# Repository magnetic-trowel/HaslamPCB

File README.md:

# HaslamPCB

Turns a product description into a manufacturable KiCad board. An LLM (or a person) writes the circuit as
Python; the tools produce the schematic, place and route the board, score its physics, and write JLCPCB
fabrication files. No step calls an LLM: every decision is a command with a traceable result.

- **[Part 1: Design a PCB](#part-1-design-a-pcb)**: use the tools on your own board.
- **[Part 2: Improve haslam](#part-2-improve-haslam)**: change the placer, router or physics and prove the change helps.

| Part | Path | Does |
|---|---|---|
| haslamsynth | `tools/research/llm-design/synth/` | circuit code → checked KiCad schematic, rules, BOM, operating intent |
| haslam | `haslam/` | placement, routing, physics evaluation |
| haslamq | `tools/haslamq/` | job queue for a shared host |
| haslamres, haslambench | `tools/haslamres/`, `bench/` | benchmark corpus, results store, experiments |

## Setup (Ubuntu, no sudo)

```bash
bench/scripts/setup.sh --all                 # KiCad 10 (apt with sudo, else Apptainer), the Freerouting fork of
                                             # bench/freerouting.ref, bench/haslam/synth venvs, ~/.cache/haslambench/env.sh
source bench/.venv/bin/activate && haslambench doctor --pipeline   # every piece below, checked
```

`env.sh` exports everything the pipeline reads: `HASLAM_HOME`, `HASLAM_KICAD_WRAP` (empty with a native KiCad; run KiCad
as `$HASLAM_KICAD_WRAP kicad-cli …` or `$HASLAM_KICAD_WRAP python3`), `KICAD10_SYMBOL_DIR`/`KICAD10_FOOTPRINT_DIR`, and with a
container KiCad `APPTAINER_BIND` (the checkout; set it yourself for a work dir elsewhere). Every shell and job:
`source ~/.cache/haslambench/env.sh`, KiCad under `ulimit -v 40000000`. The synth venv has `haslam/src` on its path; the
haslam venv has haslam installed, so no `PYTHONPATH` is needed.

On a shared host, run anything over about ten minutes or two cores through haslamq (`tools/haslamq/README.md`):
`haslamq submit --cpus N --mem XG --timeout T --owner <name> -- CMD`, then one background `haslamq wait`. Jobs run a
frozen snapshot of the checkout. Retry and cancel your own jobs only, by id or `--owner`. On a single-user machine (your
own computer, a cloud container without haslamq), run the same commands directly, long ones in the background.

---

# Part 1: Design a PCB

A design lives in `tools/research/llm-design/designs/<slug>/` (example: `solar-small`). **This table is the canonical
stage list**; [brief-to-board](docs/topics/workflow/brief-to-board.md) holds the worked example and failure modes, and
[synth/README.md](tools/research/llm-design/synth/README.md) the `design.py` API. Stages 3-11 run through
`synth/scripts/pipeline.py`, from the repo root in the haslam venv with `env.sh` sourced:

```bash
P="haslam/.venv/bin/python tools/research/llm-design/synth/scripts/pipeline.py tools/research/llm-design/designs/<slug>"
$P status          # every gate and the next stage
$P build           # then board, preflight, size, layout (once per seed), physics, warnings, review, fab
```

`pipeline.py` records each gate in `haslam-work/<slug>/pipeline/status.json`, refuses a stage while an earlier gate is
unmet or older than `design.py`/`parts.py`/`board.json`, and writes fabrication files only for a board that passed
every gate. Script paths below are relative to `tools/research/llm-design/synth/scripts/`.

| # | Stage | `pipeline.py` stage: what it runs | Gate |
|---|---|---|---|
| 1 | Requirements and parts | (you) read datasheets (tables and figures, not summaries); check stock and basic/extended status with the JLC parts API | every number has a page citation |
| 2 | Circuit as code | (you) `designs/<slug>/parts.py` (part cards), `design.py` (blocks, nets, placement relations, intent; `haslamsynth api` lists every call), `board.json` (outline, holes, fixed parts, pours, keepouts), custom footprints | — |
| 3 | Schematic and checks | `build`: `haslamsynth jlc` (LCSC numbers of generic passives, `jlc.json`), then `haslamsynth build -v` → `designs/<slug>/out/`: `.kicad_sch`, `.kicad_pro`, `.kicad_dru`, `bom.csv`, `report.md`, `<slug>.haslam_intent.json` | exit 0: 0 unwaived errors (incl. `rules.pin_escape`, `rules.pad_gap`), ERC clean, netlist round trip identical; read every warning in `report.md` |
| 4 | Unplaced board | `board`: `sch_to_board.py out board.json` at the `size` stage's best outline, else `board.json`'s | board written |
| 5 | Pre-flight | `preflight`: `preflight.py <board> --probe` (KiCad and Freerouting reachable, rules parse, schematic parity, fixed parts legal, fab profile, intent, a 3-minute place-and-route probe) | 0 FAIL; read each WARN and `blocked:` line. This is the unplaced board's gate: a plain DRC lists every unplaced part |
| 6 | Board size | `size`: `size_search.py` (start at 25 % courtyard density, shrink while DRC and `width_check.py` pass; resumable) | a passing outline |
| 7 | Layout | `layout --seed N`: `layout.sh <board> <run> <seed>` (place, route, DRC, `width_check.py`; minutes to hours) | ≥ 3 seeds routed; the best has 0 DRC errors, 0 unconnected and passes `width_check` |
| 8 | Physics | `physics`: `haslam.excite.evaluate` + `haslam.intent status` on the best seed | evaluation complete; no `hard` term violated |
| 9 | DRC warnings | `warnings`: the best seed's DRC warnings by type | each type listed in `designs/<slug>/drc_warnings.json` with a reason |
| 10 | Review | `review`: an independent review | `designs/<slug>/REVIEW.md` newer than `design.py` and `parts.py` |
| 11 | Fabrication | `fab`: `fab_outputs.py` (zone refill, DRC, Gerbers, drill, CPL, BOM) | fab-report gate passes; no blocking question open in `report.md`; `fab-report.json` lists extended parts (each a JLC setup fee) |

Where to run the long stages (`size`, `layout`, `physics`): on a single-user machine run `$P layout --seed N`
directly (in the background); on a shared host submit each through haslamq (`haslamq submit … -- $P layout --seed N`)
and wait with one background `haslamq wait`. Comparing seeds or design variants side by side (DRC by type, open
connections, every physics term): `compare_ab.py <rundir> --md table.md`.
`designs/solar-small/run_ab.sh` is solar-small's own A/B of layout recipes, not a stage.

**How each stage works** (by name; stages 1-2 are yours, the rest are `pipeline.py` stages)

- **Requirements and parts.** The designer (often an LLM) turns the product brief into numbers (voltages, currents,
  switching frequencies, limits) and picks parts that JLCPCB can assemble, preferring basic parts, which have no
  per-order setup fee.
- **Circuit as code.** The circuit is Python: part cards carry each part's pins, footprint, ratings and datasheet facts;
  `design.py` connects them into blocks and nets and states what the board must achieve; `board.json` gives the
  outline and anything mechanical that cannot move (connectors, holes, the module socket).
- **Schematic and checks.** Generic resistors and capacitors are matched to in-stock JLC parts by value, package,
  voltage and dielectric. haslamsynth checks the circuit (ratings against operating stress, ERC, netlist round trip)
  and writes the KiCad project. It derives clearance rules per net pair from each net's voltage (IPC-2221B) and track
  minimums from the finest pad pitch, and proves every pin can still escape under them. It also writes the **operating
  intent** (`<slug>.haslam_intent.json`, beside the board like `.kicad_pro`): the facts haslam cannot read from copper (rail
  voltages; each converter's input, output, current and switching frequency; cables) and the requirements, as terms
  with tiers (`hard` limits, `limit` budgets, `cost`). `python -m haslam.cli brief <board>` shows how haslam reads them.
- **Unplaced board.** The netlist becomes a `.kicad_pcb` with every footprint, the fixed parts in place, pours,
  keepouts and the fab's stackup (JLC 2-layer 1.6 mm FR-4 unless `board.json` `stackup` says otherwise).
- **Pre-flight.** A few minutes of checks catch what would waste a long run: KiCad and Freerouting reachable, rules
  accepted by KiCad, schematic parity, fixed parts legal, intent complete, and a short place-and-route probe that
  lists any connection the rules block.
- **Board size.** The outline is edge-anchored (`board_spec.py`), so the search can shrink it and re-place the fixed
  parts without hand edits.
- **Layout.** haslam places the parts (an annealer with legality checks, priced by wire length, physics terms
  and routability), routes them (Freerouting plus haslam's repair and last-mile router, which respect pad-entry,
  thermal-spoke and clearance rules), and restarts with new seeds while connections stay open, on a budget of counted
  work rather than wall time. KiCad's DRC and the width check (IPC-2221 width against each net's current) judge the
  routed board.
- **Physics.** haslam's evaluator solves the copper (layered, with 3D inductance and the stackup's capacitance) with
  every converter as a noise source and reports pickup, overshoot, emissions, losses and temperatures against the
  intent's terms. An incomplete evaluation (`why_incomplete`) prices nothing it could not compute.
- **DRC warnings and review.** Every DRC warning type gets a written reason, and an independent reviewer reads the
  design, so a board that passes the checks is still read by someone who did not write it.
- **Fabrication.** Zones are refilled, DRC must pass, and the Gerbers, drill files, pick-and-place file and BOM with
  LCSC numbers are written in JLCPCB's formats.

Judge every result by KiCad's DRC and the evaluator on the re-opened board, never by a tool's own log.

---

# Part 2: Improve haslam

haslam is improved by experiment: a change is adopted when it measurably helps on benchmark boards, paired against a
control, and never by changing how results are scored.

**Extra setup.** The corpus and harness: `source bench/.venv/bin/activate && haslambench doctor`; boards in the corpus
directory, results in `$HASLAM_RESULTS` (default `~/haslam-baselines`, `tools/haslamres/README.md`). Unit tests:
`haslam/.venv/bin/pytest haslam/tests`, `pytest bench/tests`.

**Procedure** (`docs/topics/verification/experiment-tiers.md`, `bench/suites/README.md`):

1. Branch off the weekly baseline tag (`baseline/<year>-w<week>`), make one change, add tests, push.
2. Write `$HASLAM_RESULTS/experiments/<name>/PLAN.md`: the question, the change, the suite, the primary endpoint, guards.
3. Choose the boards. A change that acts on every board runs on the sprint suites; a change to one mechanism (BGA escape,
   pours, converters, …) runs on `bench/suites/mech/<mechanism>.txt`. Limits: at most 40 CPU-h per campaign, no board
   over 0.5 CPU-h per run; larger tiers (ladder, canary) only after a sprint result.
4. Run: `python3 tools/haslamres/haslamres.py sprint <name> --base bridge|staged --commit <sha>` runs your arm against the
   stored control's runs. Smoke one or two boards first and read their runs.
5. Verdict, paired per board and seed: better, worse or undecided, with an interval, in `VERDICT.md`. Mixed results
   get a per-board look before anything is concluded.

**Rules that keep results comparable**

- Scoring code (`bench/src/haslambench/score.py`, the evaluators) defines the benchmark. A fix to it is its own commit that
  says why, and stored results are re-scored, not re-run.
- Every arm runs at the same tag, with the same Freerouting build, on counted-work budgets, side by side.
- A method's only score is `kicad-cli` on its re-opened output board.

Background: [`docs/INDEX.md`](docs/INDEX.md) (digests, then topic docs; `research_notes/` is raw evidence).

## License

Code is [GPL-3.0-or-later](LICENSE); docs and research notes CC-BY-4.0, rule packs CC0-1.0, datasets CDLA-Permissive-2.0,
model weights Apache-2.0 ([`LICENSING.md`](LICENSING.md); [`CONTRIBUTING.md`](CONTRIBUTING.md), DCO sign-off).

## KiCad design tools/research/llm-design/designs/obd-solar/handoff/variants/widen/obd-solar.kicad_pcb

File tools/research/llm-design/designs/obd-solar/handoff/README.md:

<!-- SPDX-FileCopyrightText: 2026 HaslamPCB contributors -->
<!-- SPDX-License-Identifier: CC-BY-4.0 -->
# obd-solar handoff package: boards, evaluations and how to reproduce

Scope: every file needed to study obd-solar's power-net track widths without rebuilding it. The findings are in
[docs/research/routing/power-net-track-width.md](../../../../../../docs/research/routing/power-net-track-width.md); the
run's friction log is [../FRICTION.md](../FRICTION.md); the circuit is [../design.py](../design.py) and
[../parts.py](../parts.py) (explained in [../DESIGN.md](../DESIGN.md), reviewed in [../REVIEW.md](../REVIEW.md)).
Keys: obd-solar handoff, board package, routed board, width_check, reproduction

These boards are this project's own design (GPL-3.0-or-later, like the rest of `designs/`), not corpus boards, so they
may be committed. Generated on branch `obd-solar-e2e` with KiCad 10.0.8 and the Freerouting fork pinned at 06d2686.

## Contents

| Path | What | Made by |
|---|---|---|
| `unplaced/obd-solar.kicad_pcb` | 96 x 66 mm, 2-layer JLC stackup, 94 footprints, fixed connectors, GND pours, nothing placed or routed | `haslamsynth build` + `sch_to_board.py` (outline 96 x 66) |
| `unplaced/obd-solar.kicad_pro`, `.kicad_dru` | net classes sized from each net's current (10 C rise), JLC fab profile (board setup + FAB rules), functional spacing rules | haslamsynth |
| `unplaced/obd-solar.haslam_intent.json` | operating facts (rails, 3 commutation cells, J301 load 1 A typ / 2 A max), terms (FB/MPPT pickup, overshoot, heat.track 20 K, drop.rail VBUS 150 mV, Tj), 35 placement relations (hot loops as requested near) | haslamsynth |
| `unplaced/netlist.json` | every pin's net, each net's `i_max`, `board.trace_rise_c` | haslamsynth |
| `unplaced/bom.csv`, `fp-lib-table`, `sym-lib-table` | BOM with LCSC numbers; library tables (custom footprints in `../footprints/custom.pretty`) | haslamsynth |
| `routed-s1/obd-solar.kicad_pcb` | seed 1 of `layout.sh` (restart.py recipe, HASLAM_TIME 1200), **before** any power-copper post-pass; this is the board measured in the research doc | `layout.sh` |
| `routed-s1/eval/drc.json` | KiCad DRC with schematic parity: 4 `starved_thermal`, 0 unconnected, parity 0 | kicad-cli |
| `routed-s1/eval/width.json`, `width.txt` | branch-current width gate: 7 nets too narrow (VBAT 69.7 mm, VBUS 20.9, CHG_OUT 41.7, BB_SW2 25.8, OBD_RAW 8.6, BB_SW1 6.8, ...) | `width_check.py` |
| `routed-s1/eval/excite.json`, `status.json` | physics evaluation (0.125 mm cell windows): hottest track 199.6 K, VBUS drop 266 mV, U301 Tj 185 C, FB pickup 259 mV, copper loss 1.76 W | `haslam.excite.evaluate`, `haslam.intent status` |
| `variants/widen/` | `routed-s1` after `power_copper` (widen mode): VBAT 68.2 / VBUS 15.5 / CHG_OUT 11.2 mm too narrow, DRC 4 | `haslam.route.power_copper` |
| `variants/zones-into-pads/` | after `power_copper --mode vector --vector-out zones --no-neck` (67 zones pour into SMD pads): 65.2 / 11.8 / 8.3 mm, DRC 3 | same |

`width_check.py` takes every net's DC current paths from the evaluator's plan under the intent file beside the board (the
hand-written `width_injections.json` it once needed for the OBD feed, VBAT, PV_IN, CHG_OUT and the switch nodes was removed
once the plan covered them: FRICTION.md #73).

## Reproduce

From the repo root, in the haslam venv with `~/.cache/haslambench/env.sh` sourced and `PYTHONPATH=haslam/src`:

```bash
H=tools/research/llm-design/designs/obd-solar/handoff
python tools/research/llm-design/synth/scripts/width_check.py $H/routed-s1/obd-solar.kicad_pcb $H/unplaced/netlist.json
```

```bash
python -m haslam.route.power_copper $H/routed-s1/obd-solar.kicad_pcb /tmp/pc/obd-solar.kicad_pcb --mode vector --vector-out zones --no-neck
```

Route the unplaced board again (copy `unplaced/` to a work folder first; a renamed board runs on KiCad's default rules):

```bash
HASLAM_TIME=1200 HASLAM_EVAL=0 bash tools/research/llm-design/synth/scripts/layout.sh <work>/obd-solar.kicad_pcb <outdir> 1
```

Rebuild everything from source instead: `python tools/research/llm-design/synth/scripts/pipeline.py tools/research/llm-design/designs/obd-solar build`,
then `board`, `preflight`, `layout` (see the script's docstring for the gates).

## Notes

1. `routed-s1` was placed and routed before the hot-loop `requested` relations and the J301 load fact were added to the
   intent; its copy of the intent file is the current one (used for the evaluation). The unplaced board's intent is current.
2. Zones written by power_copper are unfilled until refilled (`synth/scripts/refill.py`, KiCad's Python); the variant boards
   here are refilled.
3. Smoke A/B of the router change (`gfix-route-width` + `bridge.neckdown=1` vs the current recipe) on `unplaced/` was running when
   this package was written; results go into FRICTION.md.

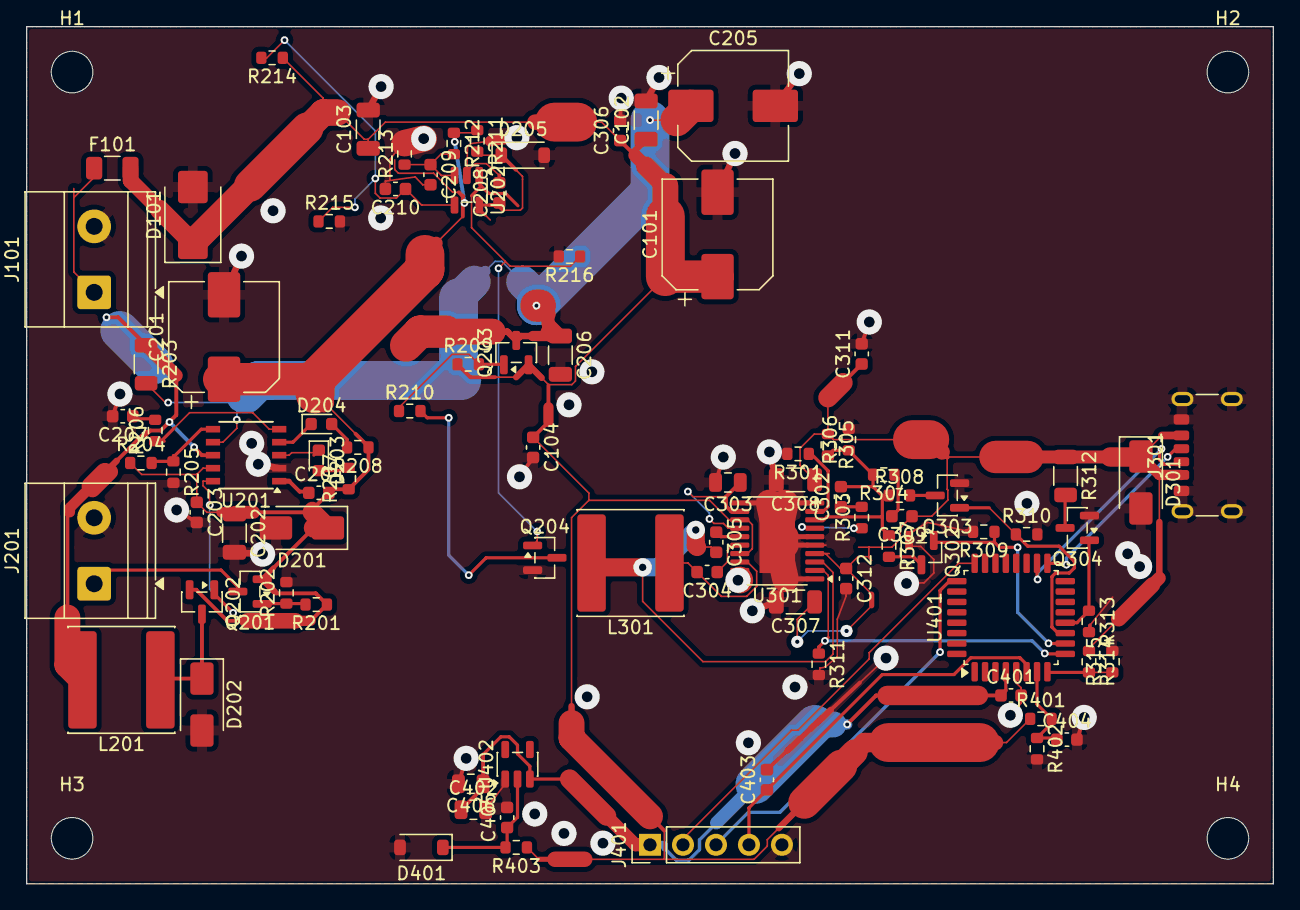
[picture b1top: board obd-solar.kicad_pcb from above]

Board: 2 copper layers, 96.0 x 66.0 mm, 94 parts (0 on the bottom side), 51 nets.

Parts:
C101, C201, C205: 100uF; CP_Elec_8x10
C102, C103, C202, C206: 10uF; C_1206_3216Metric
C104, C203, C204, C208, C304, C305, C306, C311, C401, C403, C404: 100nF; C_0603_1608Metric
C207: 220nF; C_0603_1608Metric
C209, C210: 10nF; C_0603_1608Metric
C302: 820pF; C_0603_1608Metric
C303, C402: 4.7uF; C_0805_2012Metric
C307, C308: 22uF; C_1206_3216Metric
C309: 33pF; C_0603_1608Metric
C312, C405: 1uF; C_0603_1608Metric
C406: 2.2uF; C_0805_2012Metric
D101: SMBJ24A; D_SMB
D201: SMAJ26A; D_SMA
D202: SS34; D_SMA
D203: red; LED_0603_1608Metric
D204: green; LED_0603_1608Metric
D205: BZT52C5V6; D_SOD-123
D301: SMAJ15A; D_SMA
D401: BZT52C27; D_SOD-123
F101: 5A; Fuse_1206_3216Metric
H1, H2, H3, H4: MountingHole; MountingHole_3.2mm_M3
J101, J201: KF128-5.08-2P-AA; TerminalBlock_Phoenix_MKDS-1,5-2-5.08_1x02_P5.08mm_Horizont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
J301: USB4125-GF-A; USB_C_Receptacle_GCT_USB4125-xx-x_6P_TopMnt_Horizontal
J401: DNP; PinHeader_1x05_P2.54mm_Vertical
L201: 47uH; L_Sunlord_SWPA8040S
L301: 10uH; L_Sunlord_SWPA8040S
Q201, Q202, Q203: AO3407A; SOT-23
Q204, Q302, Q303: 2N7002; SOT-23
Q304: AO3400A; SOT-23
R201: 4.7M; R_0603_1608Metric
R202: 8.2M; R_0603_1608Metric
R203: 0.18; R_1206_3216Metric
R204: 1.27M; R_0603_1608Metric
R205, R211, R314: 100k; R_0603_1608Metric
R206: 120; R_0603_1608Metric
R207, R208, R304, R315: 10k; R_0603_1608Metric
R209, R210, R215, R216, R305, R309, R310, R311, R313, R402: 1M; R_0603_1608Metric
R212, R214, R401: 10M; R_0603_1608Metric
R213: 976k; R_0603_1608Metric
R301: 35.7k; R_0603_1608Metric
R303: 40.2k; R_0603_1608Metric
R306, R307: 249k; R_0603_1608Metric
R308: 340k; R_0603_1608Metric
R312: 470; R_1206_3216Metric
R403: 1k; R_0603_1608Metric
U201: CN3767; SSOP-10_3.9x4.9mm_P1.00mm
U202: TLV7031DBVR; SOT-23-5
U301: LTC3115EFE-1#PBF; LTC_FE20_EP2.74x4.95
U401: STM32G071KBT6; LQFP-32_7x7mm_P0.8mm
U402: TPS709B33DBVR; SOT-23-5

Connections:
+3V3: C401.1, C402.1, C406.1, J401.1, U401.4 (VDD), U402.3 (OUT)
/BLK/CMP_INN: C210.1, R214.2, R215.1, U202.4 (IN-)
/BLK/CMP_INP: C209.1, R212.2, R213.1, U202.3 (IN+)
/BLK/CMP_OUT: Q204.1 (G), R216.1, U202.1 (OUT)
/BLK/CMP_VCC: C208.1, D205.1 (K), R211.2, U202.5 (V+)
/BLK/QB_G: Q203.1 (G), R209.2, R210.1
/BLK/QB_PD: Q204.3 (D), R210.2
/CHG/CHG_CS: L201.2, R203.1, U201.8 (CSP)
/CHG/CHRG_N: D203.1 (K), U201.3 (CHRG)
/CHG/COMP_RC: R206.1, U201.5 (COM)
/CHG/COMP_Z: C207.1, R206.2
/CHG/DONE_N: D204.1 (K), U201.4 (DONE)
/CHG/DRV: Q202.1 (G), U201.10 (DRV)
/CHG/LEDG_A: D204.2 (A), R208.2
/CHG/LEDR_A: D203.2 (A), R207.2
/CHG/MPPT: R204.2, R205.1, U201.6 (MPPT)
/CHG/PV_G: Q201.1 (G), R201.2, R202.1
/CHG/SW_CHG: D202.1 (K), L201.1, Q202.3 (D)
/CHG/VG_CHG: C204.1, U201.1 (VG)
/CTL/LDO_IN: C405.1, D401.1 (K), R403.2, U402.2 (IN)
/CTL/NRST: C403.1, J401.4, U401.6 (PF2)
/CTL/SWCLK: J401.3, U401.25 (PA14)
/CTL/SWDIO: J401.2, U401.24 (PA13)
/USB/BB_BOOT1: C304.1, U301.16 (BST1)
/USB/BB_BOOT2: C305.1, U301.15 (BST2)
/USB/BB_CZ: C302.1, R303.2
/USB/BB_FB: C302.2, R304.2, R305.2, R306.1, R307.1, R308.1, U301.8 (FB)
/USB/BB_FF: C309.2, R304.1
/USB/BB_RT: R301.1, U301.9 (RT)
/USB/BB_SW1: C304.2, L301.1, U301.18 (SW1)
/USB/BB_SW2: C305.2, L301.2, U301.3 (SW2)
/USB/BB_VC: R303.1, U301.7 (VC)
/USB/BB_VCC: C303.1, U301.12 (VCC), U301.14 (PVCC)
/USB/DIS_D: Q304.3 (D), R312.2
/USB/FB9: Q302.3 (D), R307.2
/USB/FB12: Q303.3 (D), R308.2
BB_EN: R311.1, U301.2 (RUN), U401.9 (PA2)
CC1: J301.A5 (CC1), U401.18 (PA8)
CC2: J301.B5 (CC2), U401.17 (PB15)
CHG_OUT: C205.1, C206.1, Q203.3 (D), R203.2, U201.7 (BAT)
GND: C101.2, C102.2, C103.2, C104.2, C201.2, C202.2, C203.2, C205.2, C206.2, C207.2, C208.2, C209.2, C210.2, C303.2, C306.2, C307.2, C308.2, C311.2, C312.2, C401.2, C402.2, C403.2, C404.2, C405.2, C406.2, D101.2 (A), D201.2 (A), D202.2 (A), D205.2 (A), D301.2 (A), D401.2 (A), J101.2, J201.2, J301.A12 (GND), J301.B12 (GND), J301.SH (SHIELD), J401.5, Q204.2 (S), Q302.2 (S), Q303.2 (S), Q304.2 (S), R202.2, R205.2, R213.2, R215.2, R216.2, R301.2, R306.2, R309.2, R310.2, R311.2, R313.2, R315.2, R402.2, U201.2 (GND), U202.2 (V-), U301.1 (PGND1), U301.5 (GND1), U301.6 (GND2), U301.10 (PGND2), U301.11 (PGND3), U301.19 (PWM), U301.20 (PGND4), U301.21 (EP), U401.5 (VSS), U402.1 (GND)
OBD_RAW: F101.1, J101.1
PV_IN: C201.1, C202.1, C203.1, C204.2, D201.1 (K), Q201.2 (S), Q202.2 (S), R201.1, R204.1, R207.1, R208.1, R211.1, R212.1, U201.9 (VCC)
PV_RAW: J201.1, Q201.3 (D)
VBAT: C101.1, C102.1, C103.1, C104.1, C306.1, D101.1 (K), F101.2, Q203.2 (S), R209.1, R214.1, R401.1, R403.1, U301.13 (VIN), U301.17 (PVIN)
VBAT_SNS: C404.1, R401.2, R402.1, U401.7 (PA0)
VBUS: C307.1, C308.1, C309.1, C311.1, C312.1, D301.1 (K), J301.A9 (VBUS), J301.B9 (VBUS), R305.1, R312.1, R314.1, U301.4 (PVOUT)
VBUS_DIS: Q304.1 (G), R313.1, U401.12 (PA5)
VBUS_SNS: R314.2, R315.1, U401.8 (PA1)
VSEL9: Q302.1 (G), R309.1, U401.10 (PA3)
VSEL12: Q303.1 (G), R310.1, U401.11 (PA4)

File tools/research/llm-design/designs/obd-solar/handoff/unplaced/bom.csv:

Board,Refs,Qty,Value,MPN,Manufacturer,Footprint,Category,Description,Lifecycle,On board,Second source,Datasheet,DNP
main,C104 C203 C204 C208 C304 C305 C306 C311 C401 C403 C404,11,100nF,generic,,Capacitor_SMD:C_0603_1608Metric,capacitor_ceramic,Capacitor 100nF 50V X7R 0603,active,yes,,,
main,C209 C210,2,10nF,generic,,Capacitor_SMD:C_0603_1608Metric,capacitor_ceramic,Capacitor 10nF 16V X7R 0603,active,yes,,,
main,C102 C103 C202 C206,4,10uF,generic,,Capacitor_SMD:C_1206_3216Metric,capacitor_ceramic,Capacitor 10uF 50V X5R 1206,active,yes,,,
main,C312 C405,2,1uF,generic,,Capacitor_SMD:C_0603_1608Metric,capacitor_ceramic,Capacitor 1uF 25V X7R 0603,active,yes,,,
main,C406,1,2.2uF,generic,,Capacitor_SMD:C_0805_2012Metric,capacitor_ceramic,Capacitor 2.2uF 10V X5R 0805,active,yes,,,
main,C207,1,220nF,generic,,Capacitor_SMD:C_0603_1608Metric,capacitor_ceramic,Capacitor 220nF 16V X7R 0603,active,yes,,,
main,C307 C308,2,22uF,generic,,Capacitor_SMD:C_1206_3216Metric,capacitor_ceramic,Capacitor 22uF 25V X5R 1206,active,yes,,,
main,C309,1,33pF,generic,,Capacitor_SMD:C_0603_1608Metric,capacitor_ceramic,Capacitor 33pF 50V C0G 0603,active,yes,,,
main,C303 C402,2,4.7uF,generic,,Capacitor_SMD:C_0805_2012Metric,capacitor_ceramic,Capacitor 4.7uF 10V X5R 0805,active,yes,,,
main,C302,1,820pF,generic,,Capacitor_SMD:C_0603_1608Metric,capacitor_ceramic,Capacitor 820pF 25V C0G 0603,active,yes,,,
main,C101 C201 C205,3,100uF,BXJ 35V100 8*10,Lelon,Capacitor_SMD:CP_Elec_8x10,capacitor_electrolytic,Polarized capacitor 100uF 35V,active,yes,,https://www.lcsc.com/datasheet/C165636.pdf,
main,D401,1,BZT52C27,BZT52C27,,Diode_SMD:D_SOD-123,diode,D_Zener 28.35V 0.018A,active,yes,,https://www.lcsc.com/datasheet/C173421.pdf,
main,D205,1,BZT52C5V6,BZT52C5V6,,Diode_SMD:D_SOD-123,diode,D_Zener 6.0V 0.08A,active,yes,,https://www.lcsc.com/datasheet/C2119.pdf,
main,D204,1,green,KT-0603G,,LED_SMD:LED_0603_1608Metric,led,LED green 0603,active,yes,,,
main,D203,1,red,KT-0603R,,LED_SMD:LED_0603_1608Metric,led,LED red 0603,active,yes,,,
main,D301,1,SMAJ15A,SMAJ15A,Littelfuse,Diode_SMD:D_SMA,tvs,D_TVS 15V 16.4A,active,yes,,https://www.littelfuse.com/assetdocs/littelfuse-tvs-diode-sm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,
main,D201,1,SMAJ26A,SMAJ26A,Littelfuse,Diode_SMD:D_SMA,tvs,D_TVS 26V 9.5A,active,yes,,https://www.littelfuse.com/assetdocs/littelfuse-tvs-diode-sm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,
main,D101,1,SMBJ24A,SMBJ24A,Littelfuse,Diode_SMD:D_SMB,tvs,D_TVS 24V 15.5A,active,yes,,https://www.littelfuse.com/assetdocs/littelfuse-tvs-diode-sm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,
main,D202,1,SS34,SS34,MDD,Diode_SMD:D_SMA,diode,D_Schottky 40V 3A,active,yes,,https://www.lcsc.com/datasheet/C8678.pdf,
main,F101,1,5A,0466005.NRHF,Littelfuse,Fuse:Fuse_1206_3216Metric,fuse,Fuse 5A 32V,active,yes,,https://www.littelfuse.com/assetdocs/littelfuse-fuse-466-datasheet,
main,J401,1,DNP,DNP,,Connector_PinHeader_2.54mm:PinHeader_1x05_P2.54mm_Vertical,connector,Connector 5 pins,active,yes,,https://www.lcsc.com/datasheet/C2337.pdf,yes
main,J101 J201,2,KF128-5.08-2P-AA,KF128-5.08-2P-AA,Cixi Kefa,"TerminalBlock_Phoenix:TerminalBlock_Phoenix_MKDS-1,5-2-5.08_1x02_P5.08mm_Horizontal",connector,Connector 2 pins,active,yes,,https://www.lcsc.com/datasheet/C474952.pdf,
main,J301,1,USB4125-GF-A,USB4125-GF-A,GCT,Connector_USB:USB_C_Receptacle_GCT_USB4125-xx-x_6P_TopMnt_Horizontal,connector,Connector 6 pins,active,yes,,https://gct.co/files/drawings/usb4125.pdf,
main,L301,1,10uH,SWPA8040S100MT,Sunlord,Inductor_SMD:L_Sunlord_SWPA8040S,inductor,Inductor 10uH 3.3A,active,yes,,https://www.sunlordinc.com/,
main,L201,1,47uH,SWPA8040S470MT,Sunlord,Inductor_SMD:L_Sunlord_SWPA8040S,inductor,Inductor 47uH 1.55A,active,yes,,https://www.sunlordinc.com/,
main,Q204 Q302 Q303,3,2N7002,2N7002,Jiangsu Changjing,Package_TO_SOT_SMD:SOT-23,mosfet,N-MOSFET 60V 0.115A,active,yes,,https://www.onsemi.com/pdf/datasheet/2n7002-d.pdf,
main,Q304,1,AO3400A,AO3400A,Alpha & Omega,Package_TO_SOT_SMD:SOT-23,mosfet,N-MOSFET 30V 5.7A,active,yes,,https://www.aosmd.com/res/datasheets/AO3400A.pdf,
main,Q201 Q202 Q203,3,AO3407A,AO3407A,Alpha & Omega,Package_TO_SOT_SMD:SOT-23,mosfet,P-MOSFET 30V 4.2A,active,yes,,https://www.aosmd.com/res/datasheets/AO3407A.pdf,
main,R204,1,1.27M,generic,,Resistor_SMD:R_0603_1608Metric,resistor,Resistor 1.27M 1% 0603,active,yes,,,
main,R205 R211 R314,3,100k,generic,,Resistor_SMD:R_0603_1608Metric,resistor,Resistor 100k 1% 0603,active,yes,,,
main,R212 R214 R401,3,10M,generic,,Resistor_SMD:R_0603_1608Metric,resistor,Resistor 10M 1% 0603,active,yes,,,
main,R207 R208 R304 R315,4,10k,generic,,Resistor_SMD:R_0603_1608Metric,resistor,Resistor 10k 1% 0603,active,yes,,,
main,R206,1,120,generic,,Resistor_SMD:R_0603_1608Metric,resistor,Resistor 120 1% 0603,active,yes,,,
main,R209 R210 R215 R216 R305 R309 R310 R311 R313 R316 R402,11,1M,generic,,Resistor_SMD:R_0603_1608Metric,resistor,Resistor 1M 1% 0603,active,yes,,,
main,R403,1,1k,generic,,Resistor_SMD:R_0603_1608Metric,resistor,Resistor 1k 1% 0603,active,yes,,,
main,R306 R307,2,249k,generic,,Resistor_SMD:R_0603_1608Metric,resistor,Resistor 249k 1% 0603,active,yes,,,
main,R308,1,340k,generic,,Resistor_SMD:R_0603_1608Metric,resistor,Resistor 340k 1% 0603,active,yes,,,
main,R301,1,35.7k,generic,,Resistor_SMD:R_0603_1608Metric,resistor,Resistor 35.7k 1% 0603,active,yes,,,
main,R201,1,4.7M,generic,,Resistor_SMD:R_0603_1608Metric,resistor,Resistor 4.7M 1% 0603,active,yes,,,
main,R303,1,40.2k,generic,,Resistor_SMD:R_0603_1608Metric,resistor,Resistor 40.2k 1% 0603,active,yes,,,
main,R312,1,470,generic,,Resistor_SMD:R_1206_3216Metric,resistor,Resistor 470 1% 1206,active,yes,,,
main,R202,1,8.2M,generic,,Resistor_SMD:R_0603_1608Metric,resistor,Resistor 8.2M 1% 0603,active,yes,,,
main,R213,1,976k,generic,,Resistor_SMD:R_0603_1608Metric,resistor,Resistor 976k 1% 0603,active,yes,,,
main,R203,1,0.18,RTT06R180FTP,Ralec,Resistor_SMD:R_1206_3216Metric,resistor,Resistor 0.18 1% 1206,active,yes,,https://www.lcsc.com/datasheet/C104934.pdf,
main,U201,1,CN3767,CN3767,Consonance,Package_SO:SSOP-10_3.9x4.9mm_P1.00mm,ic,"4 A 12 V lead-acid PWM buck charger: trickle, CC, over-charge (14.8 V), float (13.55 V), CV-MPPT",active,yes,,https://www.hestore.eu/prod_getfile.php?id=19038,
main,U301,1,LTC3115EFE-1#PBF,LTC3115EFE-1#PBF,Analog Devices,custom:LTC_FE20_EP2.74x4.95,ic,"40 V 2 A synchronous buck-boost, 3 uA shutdown, Burst Mode, output disconnect",active,yes,,https://www.analog.com/media/en/technical-documentation/data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,
main,U401,1,STM32G071KBT6,STM32G071KBT6,STMicroelectronics,Package_QFP:LQFP-32_7x7mm_P0.8mm,ic,"Cortex-M0+ with UCPD (USB PD PHY): USB-C source policy, battery guard",active,yes,,https://www.st.com/resource/en/datasheet/stm32g071kb.pdf,
main,U202,1,TLV7031DBVR,TLV7031DBVR,Texas Instruments,Package_TO_SOT_SMD:SOT-23-5,ic,"nanopower comparator, 315 nA, push-pull, fail-safe inputs",active,yes,,https://www.ti.com/lit/ds/symlink/tlv7031.pdf,
main,U402,1,TPS709B33DBVR,TPS709B33DBVR,Texas Instruments,Package_TO_SOT_SMD:SOT-23-5,ic,"150 mA 30 V LDO, 1 uA Iq, 3.3 V",active,yes,,https://www.ti.com/lit/ds/symlink/tps709.pdf,

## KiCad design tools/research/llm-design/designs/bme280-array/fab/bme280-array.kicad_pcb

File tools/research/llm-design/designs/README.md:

# Designs

Boards designed from plain-language briefs with [`haslamsynth`](../synth/README.md). Each folder has:

- `DESIGN.md`: requirements, hazards, trade study, calculations, parts, placement;
- `CONNECTIONS.md`: net tables and naming rules;
- `parts.py` and `design.py`: the circuit as code;
- `REVIEW.md`: an independent review and the designer's response, following the
  [design review checklist](../../../../docs/topics/workflow/design-review-checklist.md) (pin semantics of every
  mode/enable/strap pin, re-review after a part swap, vehicle transients, citations for every claim);
- `out/`: the generated KiCad 10 project, `<slug>.haslam_intent.json` (operating intent for haslam), BOM and
  `report.md`. Only `report.md` and `erc.json` are committed here; rebuild the rest with
  `haslamsynth build designs/<slug>/design.py -v` (deterministic up to the title-block date, `--date`).

Taking a design to a routed board: the stage table in [README Part 1](../../../../README.md#part-1-design-a-pcb).

Write-up: [docs/research/llm-design](../../../../docs/research/llm-design/README.md).
Licensing: our files are GPL-3.0-or-later (docs CC-BY-4.0); the Phoenix Contact footprint in
`liion-balancer/footprints/` is copied from the KiCad library (CC-BY-SA-4.0 with the KiCad
libraries exception), see `REUSE.toml`.

| Design | What it is | Parts | Status |
|---|---|---|---|
| [rpi-mains-relay](rpi-mains-relay/) | Pi Zero 2 W switching six 120 V receptacles, one polycarbonate enclosure, on-board listed 5 V supply, hardware heartbeat watchdog | ~70 | Reviewed twice. Checks pass; 4 blocking questions |
| [liion-balancer](liion-balancer/) | 13–16S home-pack active balancer: per-cell isolated flyback (LT8584) + ADBMS1818, hardware trips, BMS-OK enable | 448 | Reviewed. Checks pass; 6 blocking questions |
| [leadacid-balancer](leadacid-balancer/) | 2–4 × 12 V lead-acid switched-capacitor balancer, MCU-free, fail-safe alarm | ~390 | Reviewed. Checks pass; 4 blocking questions |
| [solar-small](solar-small/) | <= 10 W, 25 V solar charger for a 12 V lead-acid / 4S LiFePO4 battery: LTC3130 in RUN-hiccup mode, DAC-set charge voltage and panel point, LTC2959 coulomb counter, FireBeetle 2 ESP32-C6; taken through haslam place/route and physics scoring ([brief-to-board](../../../../docs/topics/workflow/brief-to-board.md)) | 68 | Checks pass; routed clean at 120 x 90 mm (one seed); not reviewed |
| [prius-solar-mppt](prius-solar-mppt/) | 2017 Prius Prime roof solar: 2 × 32 C60 strings, MPPT, isolated step-up into the Li-ion pack, car on or off, current-capped, 3-layer OV; main and battery-end boards | 485 | Reviewed. Checks pass; 6 blocking questions |

"Checks pass" means 0 errors, a clean KiCad ERC, and a schematic netlist identical to
the design. Remaining check findings are waived with written reasons in `out/report.md`.

**None of these is ready to fabricate.** Each has blocking questions that only the owner, an
installer or a certification body can answer, listed in its `out/report.md`. They have not
been simulated in SPICE, built, or reviewed by a licensed engineer.

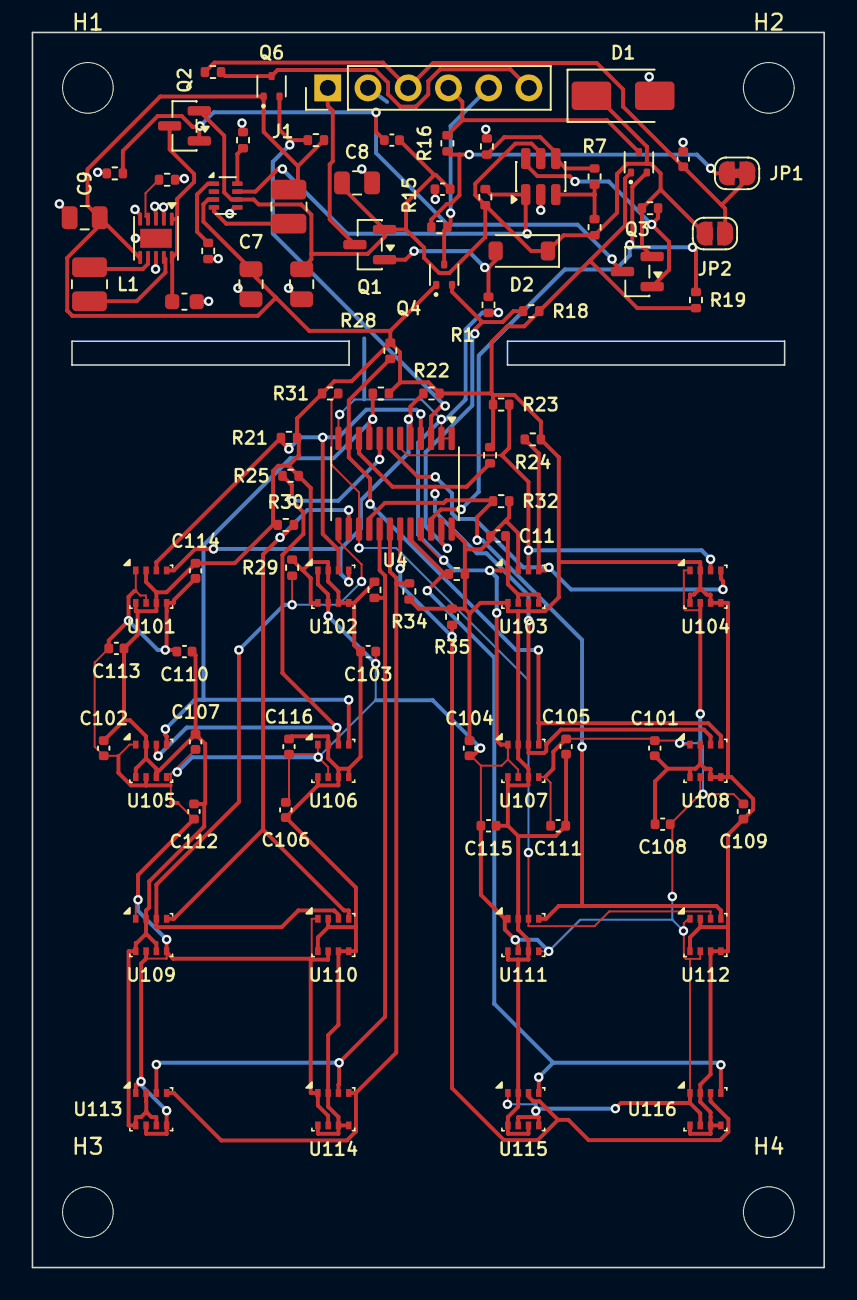
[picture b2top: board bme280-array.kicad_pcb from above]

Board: 2 copper layers, 50.0 x 78.0 mm, 94 parts (0 on the bottom side), 41 nets.

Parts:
C1, C8: 10uF; C_0805_2012Metric
C2, C10, C11, C101, C102, C103, C104, C105, C106, C107, C108, C109, C110, C111, C112, C113, C114, C115, C116: 100nF; C_0402_1005Metric
C5: 1nF; C_0402_1005Metric
C6: 10uF; C_0603_1608Metric
C7, C9: 22uF; C_0805_2012Metric
D1: SMAJ15A; D_SMA
D2: BZT52C10; D_SOD-123
H1, H2, H3, H4: MountingHole; MountingHole_3.2mm_M3
J1: PinHeader 1x6 2.54; PinHeader_1x06_P2.54mm_Vertical
JP1: SolderJumper_2_Bridged; SolderJumper-2_P1.3mm_Bridged_RoundedPad1.0x1.5mm
JP2: SolderJumper_2_Open; SolderJumper-2_P1.3mm_Open_RoundedPad1.0x1.5mm
L1, L2: 2.2uH; L_1008_2520Metric
Q1, Q2: AO3401A; SOT-23
Q3: LBSS84LT1G; SOT-23
Q4, Q5, Q6: DMG1012T-7; SOT-523
R1, R9, R10, R11: 10M; R_0402_1005Metric
R6: 9.1M; R_0402_1005Metric
R7: 220k; R_0402_1005Metric
R8: 1M; R_0402_1005Metric
R12: 1.15k; R_0402_1005Metric
R13: 42.2k; R_0402_1005Metric
R14: 34k; R_0402_1005Metric
R15, R16, R18, R19: 4.7k; R_0402_1005Metric
R17, R20: 100k; R_0402_1005Metric
R21, R22, R23, R24, R25, R26, R27, R28, R29, R30, R31, R32, R33, R34, R35, R36: 10k; R_0402_1005Metric
U1: TPS63900DSKR; WSON-10-1EP_2.5x2.5mm_P0.5mm_EP1.2x2mm
U2: TPS629203DRLR; SOT-583-8
U3: TPS3700DDCR; SOT-23-6
U4: TCA9548APWR; TSSOP-24_4.4x7.8mm_P0.65mm
U101, U102, U103, U104, U105, U106, U107, U108, U109, U110, U111, U112, U113, U114, U115, U116: BME280; Bosch_LGA-8_2.5x2.5mm_P0.65mm_ClockwisePinNumbering

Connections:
+1V8: C7.1, C9.1, C11.1, C101.1, C102.1, C103.1, C104.1, C105.1, C106.1, C107.1, C108.1, C109.1, C110.1, C111.1, C112.1, C113.1, C114.1, C115.1, C116.1, L2.2, Q4.1 (G), Q5.1 (G), Q6.1 (G), R18.1, R19.1, R20.1, R21.1, R22.1, R23.1, R24.1, R25.1, R26.1, R27.1, R28.1, R29.1, R30.1, R31.1, R32.1, R33.1, R34.1, R35.1, R36.1, U1.6 (VOUT), U2.3 (VOS), U4.24 (VCC), U101.2 (CSB), U101.6 (VDDIO), U101.8 (VDD), U102.2 (CSB), U102.5 (SDO), U102.6 (VDDIO), U102.8 (VDD), U103.2 (CSB), U103.6 (VDDIO), U103.8 (VDD), U104.2 (CSB), U104.5 (SDO), U104.6 (VDDIO), U104.8 (VDD), U105.2 (CSB), U105.6 (VDDIO), U105.8 (VDD), U106.2 (CSB), U106.5 (SDO), U106.6 (VDDIO), U106.8 (VDD), U107.2 (CSB), U107.6 (VDDIO), U107.8 (VDD), U108.2 (CSB), U108.5 (SDO), U108.6 (VDDIO), U108.8 (VDD), U109.2 (CSB), U109.6 (VDDIO), U109.8 (VDD), U110.2 (CSB), U110.5 (SDO), U110.6 (VDDIO), U110.8 (VDD), U111.2 (CSB), U111.6 (VDDIO), U111.8 (VDD), U112.2 (CSB), U112.5 (SDO), U112.6 (VDDIO), U112.8 (VDD), U113.2 (CSB), U113.6 (VDDIO), U113.8 (VDD), U114.2 (CSB), U114.5 (SDO), U114.6 (VDDIO), U114.8 (VDD), U115.2 (CSB), U115.6 (VDDIO), U115.8 (VDD), U116.2 (CSB), U116.5 (SDO), U116.6 (VDDIO), U116.8 (VDD)
/IN/Q1_G: D2.2 (A), Q1.1 (G), R1.1
/LVL/VIO_PU: JP1.2 (B), R15.1, R16.1
/PWR/CFG2: R12.1, U1.4 (CFG2)
/PWR/DIV_A: R6.2, R7.1, U3.3 (INA+)
/PWR/DIV_B: R7.2, R8.1, U3.4 (INB-)
/PWR/EN_HI: R9.2, U2.7 (EN), U3.1 (OUTA)
/PWR/LX1: L1.1, U1.9 (LX1)
/PWR/LX2: L1.2, U1.7 (LX2)
/PWR/OVP_N: Q3.1 (G), R10.2, U3.6 (OUTB)
/PWR/Q2_G: C5.2, Q2.1 (G), Q3.3 (D), R11.1
/PWR/SCONF: R13.1, U2.8 (MODE/S-CONF)
/PWR/SW: L2.1, U2.4 (SW)
/PWR/VSET: R14.1, U2.1 (FB/VSET)
CH0_SCL: R22.2, U4.5 (SC0), U101.4 (SCK), U102.4 (SCK)
CH0_SDA: R21.2, U4.4 (SD0), U101.3 (SDI), U102.3 (SDI)
CH1_SCL: R24.2, U4.7 (SC1), U103.4 (SCK), U104.4 (SCK)
CH1_SDA: R23.2, U4.6 (SD1), U103.3 (SDI), U104.3 (SDI)
CH2_SCL: R26.2, U4.9 (SC2), U105.4 (SCK), U106.4 (SCK)
CH2_SDA: R25.2, U4.8 (SD2), U105.3 (SDI), U106.3 (SDI)
CH3_SCL: R28.2, U4.11 (SC3), U107.4 (SCK), U108.4 (SCK)
CH3_SDA: R27.2, U4.10 (SD3), U107.3 (SDI), U108.3 (SDI)
CH4_SCL: R30.2, U4.14 (SC4), U109.4 (SCK), U110.4 (SCK)
CH4_SDA: R29.2, U4.13 (SD4), U109.3 (SDI), U110.3 (SDI)
CH5_SCL: R32.2, U4.16 (SC5), U111.4 (SCK), U112.4 (SCK)
CH5_SDA: R31.2, U4.15 (SD5), U111.3 (SDI), U112.3 (SDI)
CH6_SCL: R34.2, U4.18 (SC6), U113.4 (SCK), U114.4 (SCK)
CH6_SDA: R33.2, U4.17 (SD6), U113.3 (SDI), U114.3 (SDI)
CH7_SCL: R36.2, U4.20 (SC7), U115.4 (SCK), U116.4 (SCK)
CH7_SDA: R35.2, U4.19 (SD7), U115.3 (SDI), U116.3 (SDI)
GND: C1.2, C2.2, C6.2, C7.2, C8.2, C9.2, C10.2, C11.2, C101.2, C102.2, C103.2, C104.2, C105.2, C106.2, C107.2, C108.2, C109.2, C110.2, C111.2, C112.2, C113.2, C114.2, C115.2, C116.2, D1.2 (A), J1.2, R1.2, R8.2, R11.2, R12.2, R13.2, R14.2, U1.2 (SEL), U1.3 (CFG1), U1.5 (CFG3), U1.8 (GND), U1.11 (GND), U2.5 (GND), U3.2 (GND), U4.1 (A0), U4.2 (A1), U4.12 (GND), U4.21 (A2), U101.1 (GND), U101.5 (SDO), U101.7 (GND), U102.1 (GND), U102.7 (GND), U103.1 (GND), U103.5 (SDO), U103.7 (GND), U104.1 (GND), U104.7 (GND), U105.1 (GND), U105.5 (SDO), U105.7 (GND), U106.1 (GND), U106.7 (GND), U107.1 (GND), U107.5 (SDO), U107.7 (GND), U108.1 (GND), U108.7 (GND), U109.1 (GND), U109.5 (SDO), U109.7 (GND), U110.1 (GND), U110.7 (GND), U111.1 (GND), U111.5 (SDO), U111.7 (GND), U112.1 (GND), U112.7 (GND), U113.1 (GND), U113.5 (SDO), U113.7 (GND), U114.1 (GND), U114.7 (GND), U115.1 (GND), U115.5 (SDO), U115.7 (GND), U116.1 (GND), U116.7 (GND)
RST_H: J1.6, Q6.3 (D), R17.2
RST_L: Q6.2 (S), R20.2, U4.3 (~RESET)
SCL_H: J1.4, Q5.3 (D), R16.2
SCL_L: Q5.2 (S), R19.2, U4.22 (SCL)
SDA_H: J1.5, Q4.3 (D), R15.2
SDA_L: Q4.2 (S), R18.2, U4.23 (SDA)
VIN_P: C1.1, C2.1, C5.1, C8.1, D1.1 (K), D2.1 (K), JP2.2 (B), Q1.2 (S), Q2.2 (S), Q3.2 (S), R6.1, R9.1, R10.1, U2.6 (VIN), U3.5 (VDD)
VIN_RAW: J1.1, Q1.3 (D)
VIO: C10.1, J1.3, JP1.1 (A), JP2.1 (A), R17.1
VLO: C6.1, Q2.3 (D), U1.1 (EN), U1.10 (VIN)

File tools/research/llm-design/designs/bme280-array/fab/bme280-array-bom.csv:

Comment,Designator,Footprint,LCSC Part #
10uF,"C1,C8",C_0805_2012Metric,C15850
100nF,"C10,C2",C_0402_1005Metric,C307331
100nF,"C101,C102,C103,C104,C105,C106,C107,C108,C109,C11,C110,C111,C112,C113,C114,C115,C116",C_0402_1005Metric,C1525
1nF,C5,C_0402_1005Metric,C1523
10uF,C6,C_0603_1608Metric,C19702
22uF,"C7,C9",C_0805_2012Metric,C45783
SMAJ15A,D1,D_SMA,C86819
BZT52C10,D2,D_SOD-123,C173431
2.2uH,"L1,L2",L_1008_2520Metric,C576403
AO3401A,"Q1,Q2",SOT-23,C15127
LBSS84LT1G,Q3,SOT-23,C8492
DMG1012T-7,"Q4,Q5,Q6",SOT-523,C20512
10M,"R1,R10,R11,R9",R_0402_1005Metric,C26082
1.15k,R12,R_0402_1005Metric,C5159680
42.2k,R13,R_0402_1005Metric,C26979
34k,R14,R_0402_1005Metric,C2933089
4.7k,"R15,R16,R18,R19",R_0402_1005Metric,C25900
100k,"R17,R20",R_0402_1005Metric,C25741
10k,"R21,R22,R23,R24,R25,R26,R27,R28,R29,R30,R31,R32,R33,R34,R35,R36",R_0402_1005Metric,C25744
9.1M,R6,R_0402_1005Metric,C2998185
220k,R7,R_0402_1005Metric,C2909335
1M,R8,R_0402_1005Metric,C26083
TPS63900DSKR,U1,WSON-10-1EP_2.5x2.5mm_P0.5mm_EP1.2x2mm,C1518762
BME280,"U101,U102,U103,U104,U105,U106,U107,U108,U109,U110,U111,U112,U113,U114,U115,U116",Bosch_LGA-8_2.5x2.5mm_P0.65mm_ClockwisePinNumbering,C92489
TPS629203DRLR,U2,SOT-583-8,C5219295
TPS3700DDCR,U3,SOT-23-6,C33002
TCA9548APWR,U4,TSSOP-24_4.4x7.8mm_P0.65mm,C130026

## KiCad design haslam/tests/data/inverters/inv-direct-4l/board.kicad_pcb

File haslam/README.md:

# haslam

Physics-first joint placement and routing for KiCad boards. Plan:
[month-plan](../docs/topics/architecture/month-plan.md); design:
[system-design](../docs/topics/architecture/system-design.md).

```bash
python3 -m venv haslam/.venv
haslam/.venv/bin/pip install -e 'haslam[dev]'
haslam/.venv/bin/pytest haslam/tests          # KiCad tests skip without pcbnew
```

## `haslam.board`

- `model`: the board model (Contract 1), dataclasses with `to_dict`/`from_dict`.
  Units are mm and degrees in KiCad board coordinates (y down). The footprint uuid is
  the part key (the loader synthesizes a stable one when a file has none or repeats one).
- `kicad_file.load(path)`: pure-Python reader for `.kicad_pcb` (KiCad 10, tolerant of
  5-9), with the sibling `.kicad_pro` and `.kicad_dru`. Old boards get the names KiCad 10
  gives them on load (`legacy_names`: overbar net names, renamed copper layers, NPTH pads
  without numbers). Median 0.05 s per board
  (max 1.1 s for a 17.7 MB file).
- `transform`: `pad_xy`, `pads_xy` (vectorized), `courtyard`; KiCad's rotation and flip
  conventions, verified against pcbnew pad by pad.
- `pcbnew_io`: `extract(path)`, `write_poses(src, dst, {uuid: (x, y, rot, side)})` and
  `verify(path)`, through KiCad's own Python in a subprocess (the writer uses KiCad's plain
  reader and writer, so nothing but poses changes). Set `HASLAM_KICAD_PYTHON`
  (a command, e.g. `/usr/bin/python3`) or `HASLAM_KICAD_WRAP` (a prefix, e.g.
  `apptainer exec ~/kicad.sif`), as for haslambench. One KiCad Python per process
  serves the calls (each in a child forked after `import pcbnew`, so outputs are as with a
  process per call, without its ~1 s start-up); `HASLAM_PCBNEW_WORKER=0` starts one per call.
- `sdiff.diff(a, b)`: structural diff of two board files (objects keyed by uuid).

Footprint frame: pad and courtyard coordinates are stored in the library frame (the
footprint as drawn, front side, 0 degrees). A pose `(x, y, rot, side)` maps a local point
`(lx, ly)` to `(x, y) + R(rot) (lx, s*ly)` with `s = -1` on the back, where
`R(a) (u, v) = (u cos a + v sin a, -u sin a + v cos a)`; a pad's angle is `rot + s*lrot`.

Acceptance against pcbnew on the prepared haslambench tasks:
`haslam/.venv/bin/python haslam/scripts/board_acceptance.py {verify,roundtrip,place,loadtime} --tasks DIR`.

`pcbnew_io` also serves `haslam.route`: `export_dsn` (KiCad's Specctra export plus what it leaves
out, and KiCad's rule engine probed per net and layer), `import_ses`, `edit_routing` (delete,
widen, add, lock and unlock tracks and vias) and `zone_fills` (zones refilled as the DRC does).

## `haslam.route`

The KiCad -> Freerouting -> KiCad bridge: every KiCad constraint reaches the router or is
enforced after import ([freerouting-constraint-bridge](../docs/topics/routing/freerouting-constraint-bridge.md)).

```bash
haslam/.venv/bin/python -m haslam.route.cli route IN.kicad_pcb OUT.kicad_pcb --seed 0 --time 600
haslambench run --adapter haslam-fr --kinds route \
  --command "haslam/.venv/bin/python -m haslam.route.cli route {input} {output} --seed {attempt} --time {timeout}"
```

**Read `blocked` when connections stay open.** The router never relaxes a board's rules. At the
end it diagnoses each connection still open (`haslam.route.blocked`, a few seconds; `--no-blocked`
turns it off) and the JSON report (last stdout line, `--report FILE`) carries a `blocked`
section, with one line per connection in the log (`blocked: ...`). Each connection gets a cause:
`congestion` (a path exists without our other copper: not a rule), `fixed copper` (the input's
own tracks of the nets named), `rule` (a board rule: the value required and the value available,
where, and its source: the `.kicad_pro` net class or board setup, a `.kicad_dru` rule by name, a
footprint, a rule area, a pad's solder-mask opening), `haslam default` (one of haslam's own limits, with
its `HASLAM_<NAME>` / `--set` override when there is one) or `geometry` (walled in by copper even with
every clearance at zero). For example:
`U2.17 CS1: needs a 0.160 mm track at (2.52, -16.60) F.Cu, minimum track width 0.200 mm (.kicad_pro
board setup minimum track width); relax to 0.160 to allow`. The caller decides: change the rule,
move a part, or accept the open connection. Under `tools/haslamres/restart.py` the kept attempt's
report goes to `restarts/report.json` and its `blocked` lines to the wrapper's log.
`python -m haslam.route.blocked ROUTED INPUT [--drc REPORT] [--out FILE]` runs the diagnosis alone.

Locked tracks and vias in the input are kept as they are; zones named `haslam-crit:...` are
obstacles for other nets. `haslam.route.effective.load(board)` gives any other router the same
numbers per net and layer (`track_width`, `via`, `clearance`, `pad_clearance`,
`edge_clearance`, `same_net_via_pitch`). Needs Freerouting 2.5.x (found as haslambench finds it)
and kicad-cli.

`haslam` never imports `haslambench` (or research scripts); methods plug into the harness with
`haslambench run --command`.

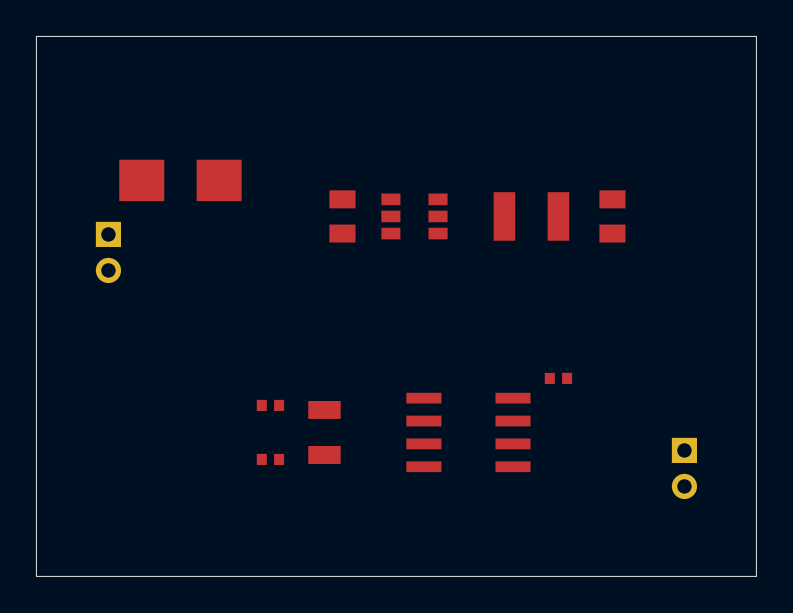
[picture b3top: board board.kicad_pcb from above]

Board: 4 copper layers, 40.0 x 30.0 mm, 12 parts (0 on the bottom side), 7 nets, no tracks yet.

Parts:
C1: 10uF; C_0805_2012Metric
C2: 22uF; C_0805_2012Metric
C3: 100nF; C_0402_1005Metric
C4, C5: 22pF; C_0402_1005Metric
D1: SMBJ24A; D_SMB
J1, J2: Conn_01x02; JST_PH_B2B-PH-K_1x02_P2.00mm_Vertical
L1: 4.7uH 3A; L_1210_3225Metric
U1: LMR51430; TSOT-23-6
U2: ATtiny85-20S; SOIC-8_3.9x4.9mm_P1.27mm
Y1: 8MHz; Crystal_SMD_3215-2Pin_3.2x1.5mm

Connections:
+3V3: C3.1, U2.8 (VCC)
+12V: C1.1, D1.1 (K), J1.1, U1.2 (EN), U1.3 (VIN)
-5V: C1.2, C2.1, J2.1, U1.4 (GND)
GND: C2.2, C3.2, C4.2, C5.2, D1.2 (A), J1.2, J2.2, L1.2, U2.4 (GND)
unnamed: L1.1, U1.5 (SW)
unnamed: C4.1, U2.2 (XTAL1/PB3), Y1.1
unnamed: C5.1, U2.3 (XTAL2/PB4), Y1.2
